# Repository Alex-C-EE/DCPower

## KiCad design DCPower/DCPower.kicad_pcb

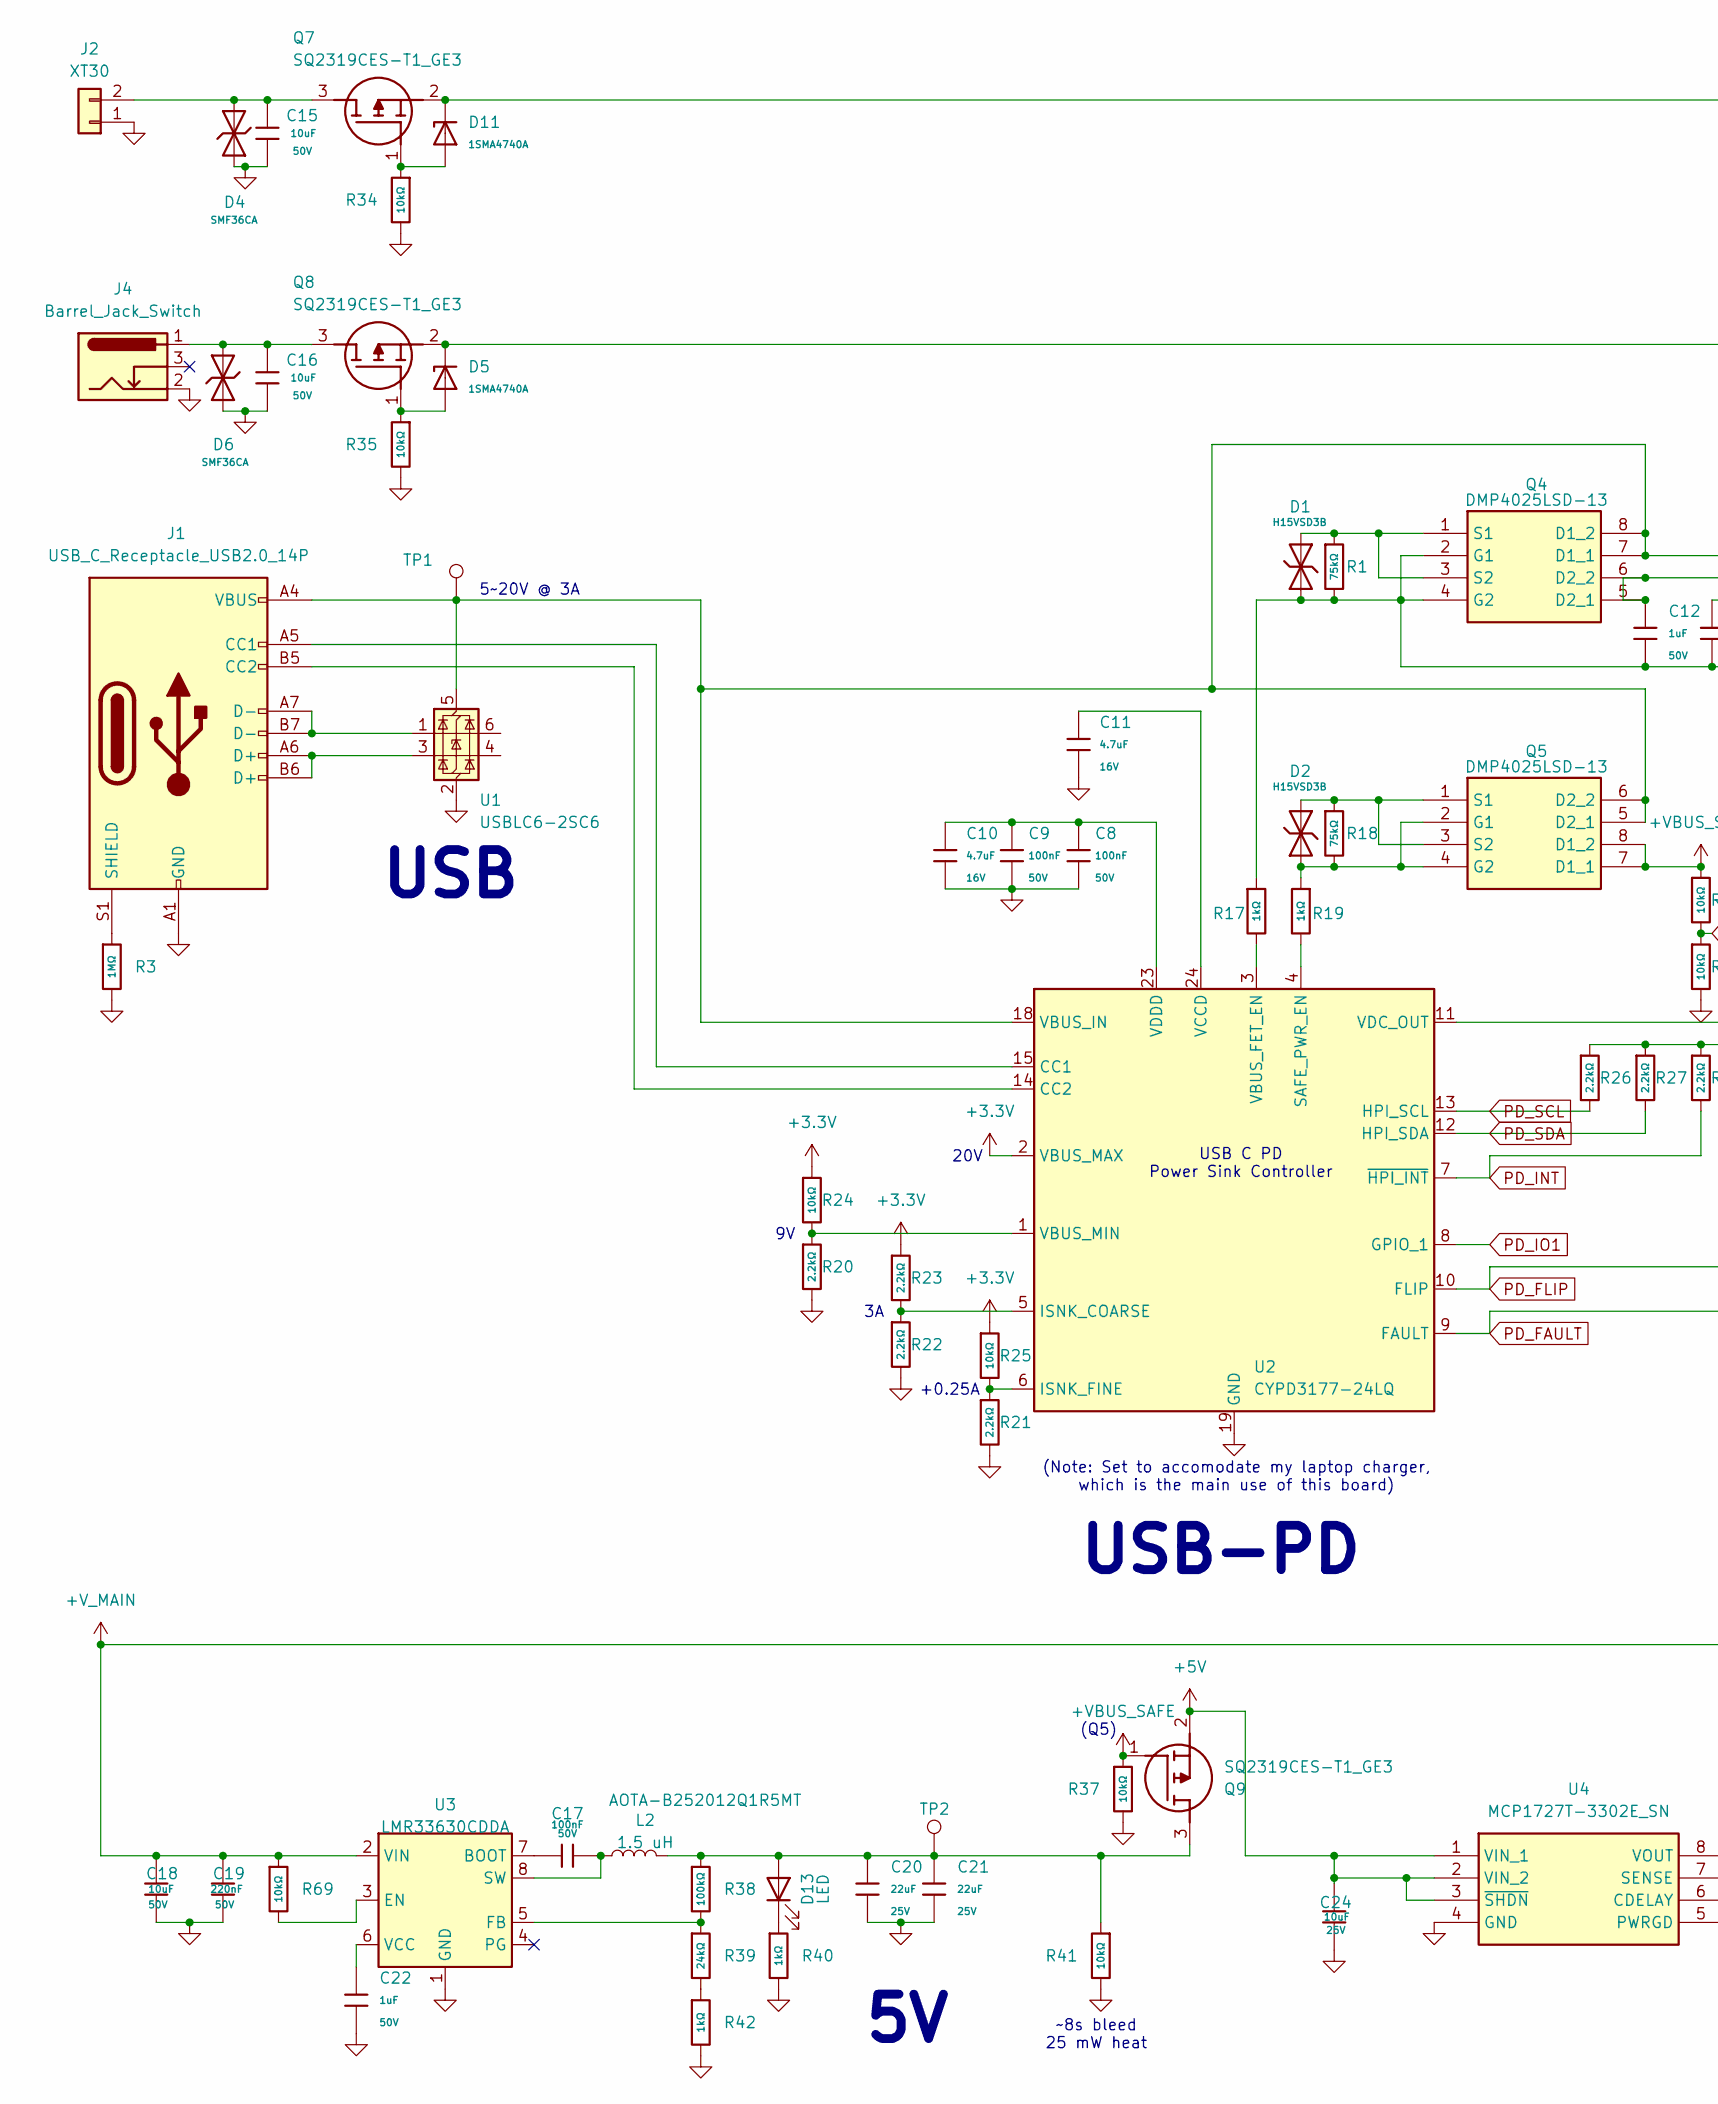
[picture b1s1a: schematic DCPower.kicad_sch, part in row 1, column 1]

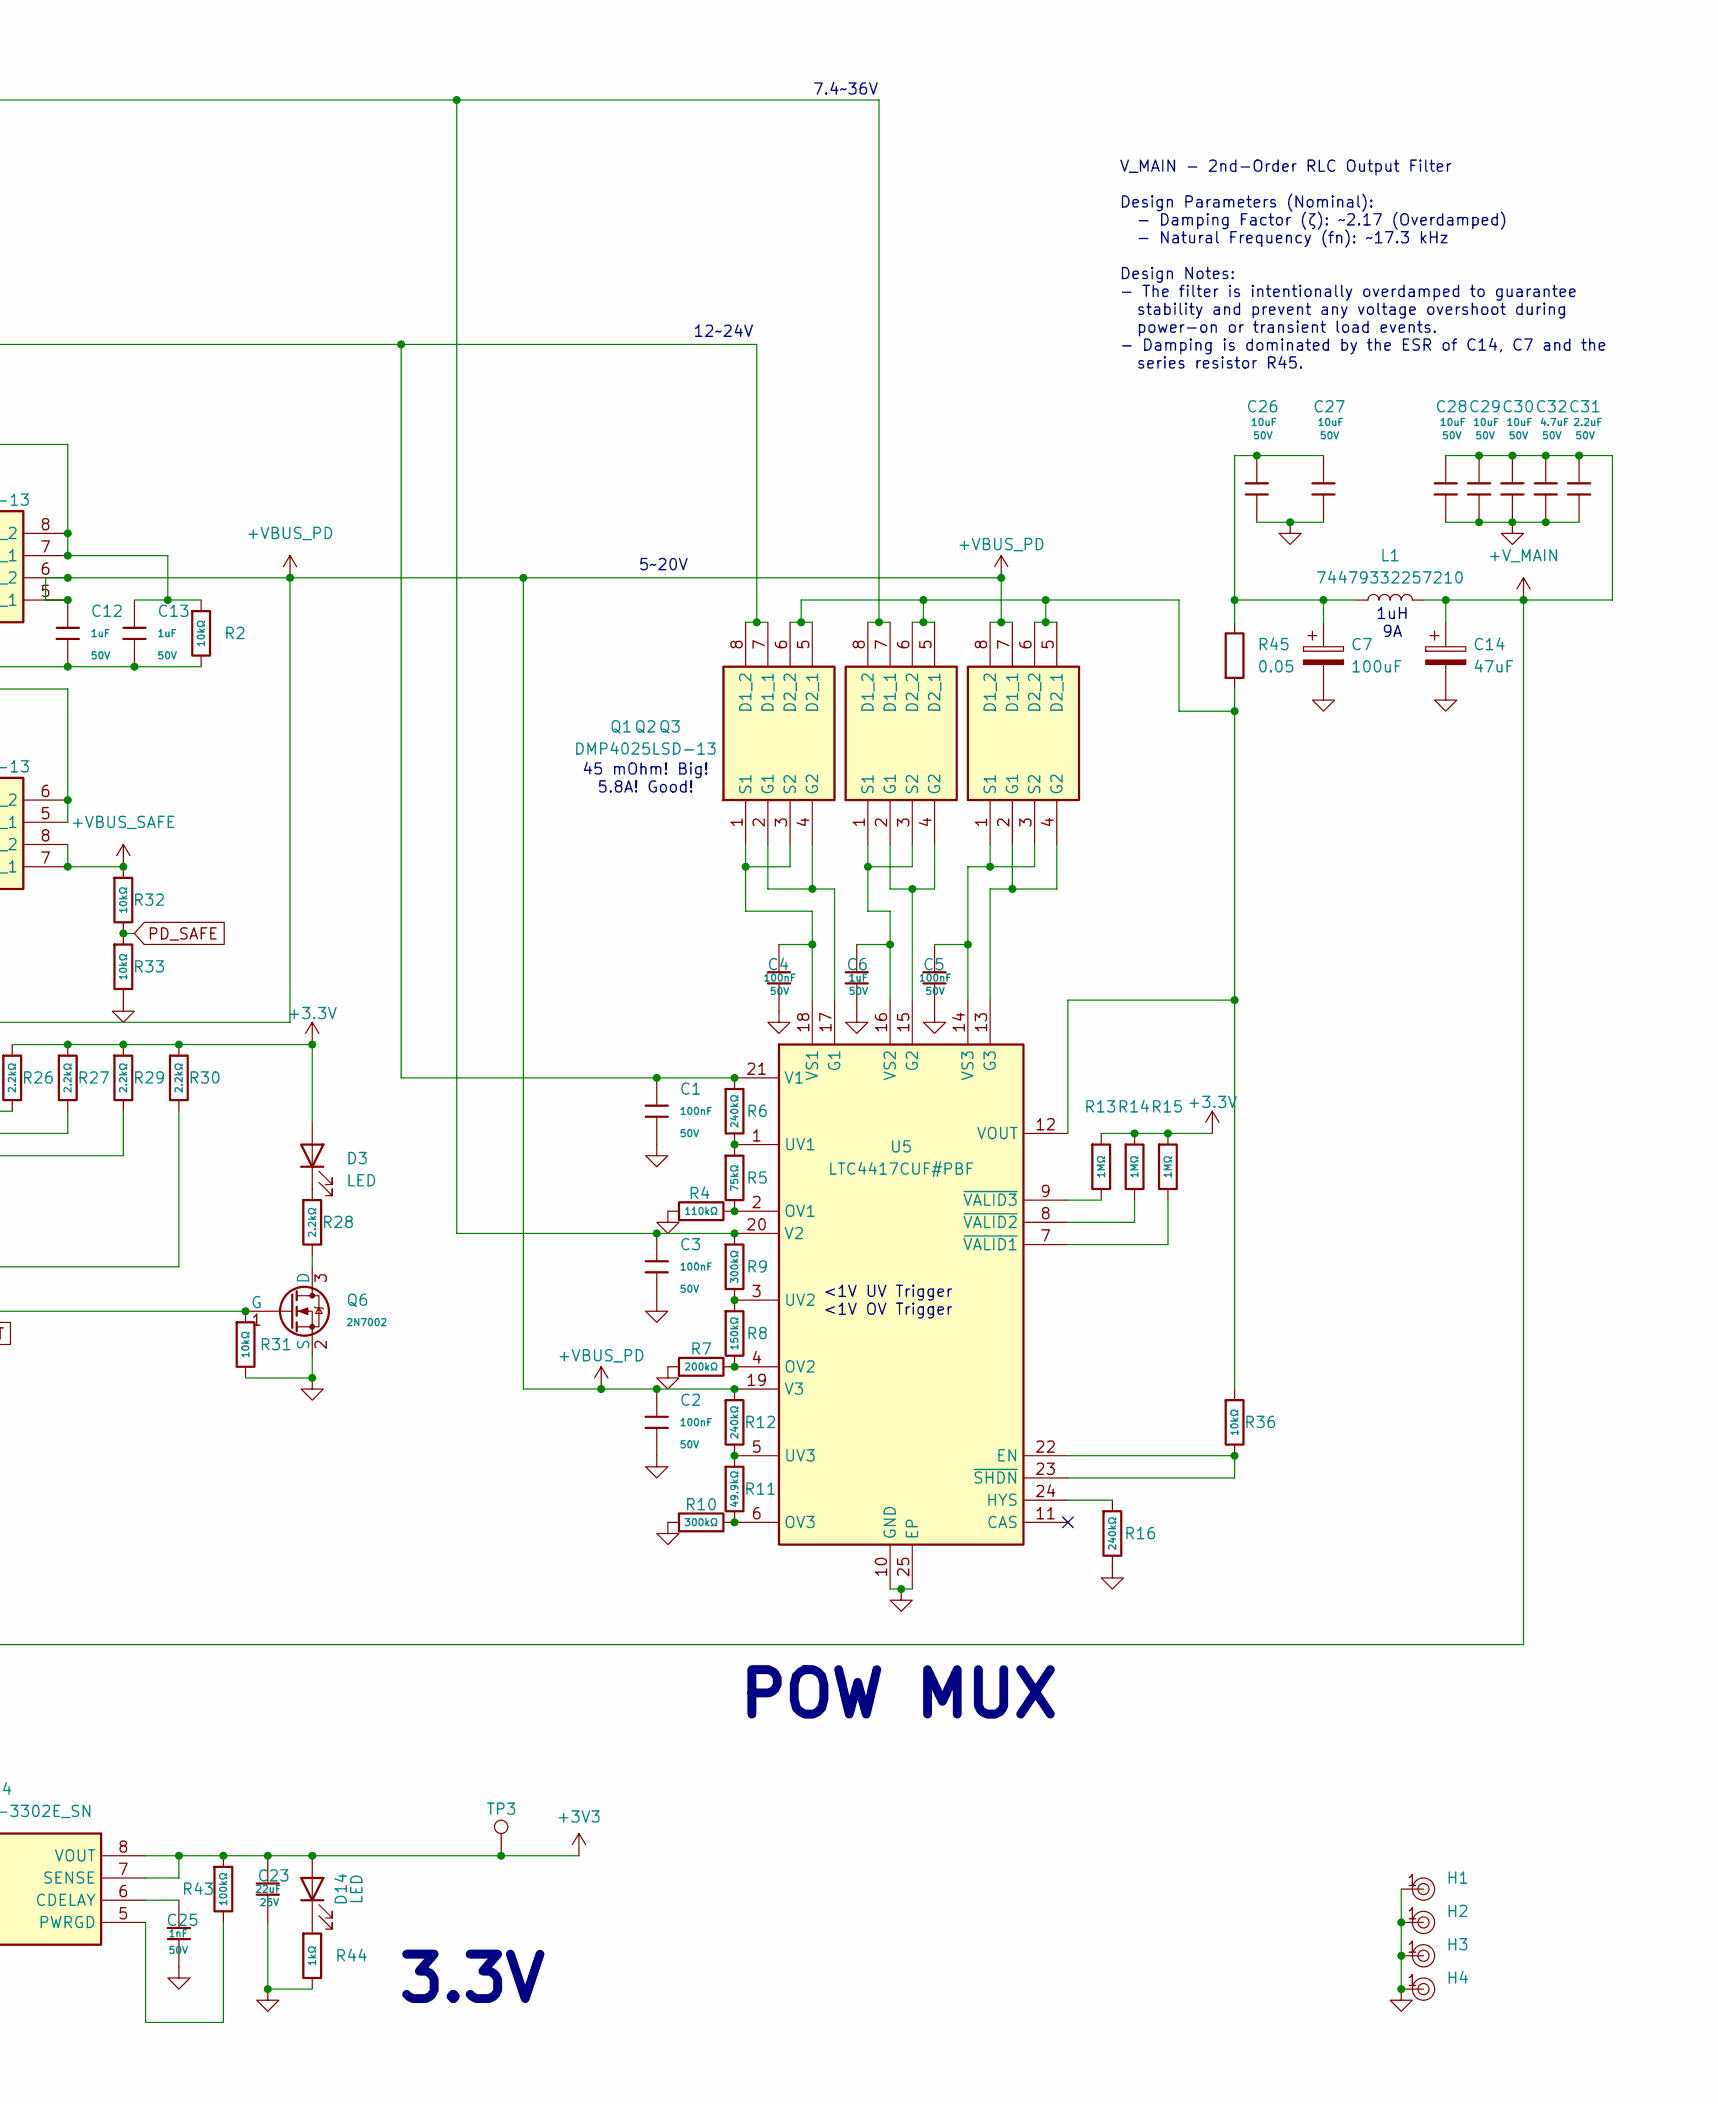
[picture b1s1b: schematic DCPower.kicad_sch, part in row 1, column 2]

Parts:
C1, C2, C3, C4, C5, C8, C9, C17: 100nF; C_0603; Voltage Rated 50V; Tolerance ±10%; Part CC0603KRX7R9BB104; LCSC C14663
C6, C12, C13: 1uF; C_0603; Voltage Rated 50V; Tolerance ±10%; Part CL10A105KB8NNNC; LCSC C15849
C7: 100uF; CAPAE830X1100N
C10, C11: 4.7uF; C_0603; Voltage Rated 16V; Tolerance ±10%; Part CL10A475KO8NNNC; LCSC C19666
C14: 47uF; EEEHP1H4R7P
C15, C16, C18: 10uF; C_0805; Voltage Rated 50V; Tolerance ±10%; Part GRM21BR61H106KE43L; LCSC C440198
C19: 220nF; C_0805; Voltage Rated 50V; Tolerance ±10%; Part CL21B224KBFNNNE; LCSC C5378
C20, C21, C23: 22uF; C_0805; Voltage Rated 25V; Tolerance ±20%; Part CL21A226MAQNNNE; LCSC C45783
C22: 1uF; C_0805; Voltage Rated 50V; Tolerance ±10%; Part CL21B105KBFNNNE; LCSC C28323
C24: 10uF; C_0805; Voltage Rated 25V; Tolerance ±10%; Part CL21A106KAYNNNE; LCSC C15850
C25: 1nF; C_0603; Voltage Rated 50V; Tolerance ±10%; Part CL10B102KB8NNNC; LCSC C1588
C26, C27, C28, C29, C30: 10uF; C_1206; Voltage Rated 50V; Tolerance ±10%; Part CL31A106KBHNNNE; LCSC C13585
C31: 2.2uF; C_0805; Voltage Rated 50V; Tolerance ±10%; Part CL21A225KBQNNNE; LCSC C377773
C32: 4.7uF; C_1206; Voltage Rated 50V; Tolerance ±10%; Part 1206B475K500NT; LCSC C29823
D1, D2: H15VSD3B; D_SOD-323; Part H15VSD3B; LCSC C20615814
D3, D13, D14: LED; LED_0603_1608Metric
D4, D6: SMF36CA; D_SOD-123FL; Part SMF36CA; LCSC C19077521
D5, D11: 1SMA4740A; D_SMA; Part 1SMA4740A; LCSC C19077479
H1, H2, H3, H4: Hole, 3mm
J1: USB_C_Receptacle_USB2.0_14P; USB_C_Receptacle_GCT_USB4105-xx-A_16P_TopMnt_Horizontal
J2: XT30; AMASS_XT30PW-M_1x02_P2.50mm_Horizontal
J4: Barrel_Jack_Switch; 694106301002_1
L1: 74479332257210; L_TDK_NLV32_3.2x2.5mm
L2: 1.5 uH; L_1008_2520Metric
Q1, Q2, Q3, Q4, Q5: DMP4025LSD-13; SOIC127P600X175-8N; Mouser Part Number 621-DMP4025LSD-13
Q6: 2N7002; Q_SOT-23; Part 2N7002; LCSC C8545
Q7, Q8, Q9: SQ2319CES-T1_GE3; SOT95P237X112-3N; Mouser Part Number 78-SQ2319CES-T1_GE3
R1, R5, R18: 75kΩ; R_0603; Overload Voltage (Max) 75V; Tolerance ±1%; Part 0603WAF7502T5E; LCSC C23242
R2, R24, R25, R31, R32, R33, R36, R37, R41, R69: 10kΩ; R_0603; Overload Voltage (Max) 75V; Tolerance ±1%; Part 0603WAF1002T5E; LCSC C25804
R3, R13, R14, R15: 1MΩ; R_0603; Overload Voltage (Max) 75V; Tolerance ±1%; Part 0603WAF1004T5E; LCSC C22935
R4: 110kΩ; R_0603; Overload Voltage (Max) 75V; Tolerance ±1%; Part 0603WAF1103T5E; LCSC C25805
R6, R12, R16: 240kΩ; R_0603; Overload Voltage (Max) 75V; Tolerance ±1%; Part 0603WAF2403T5E; LCSC C4197
R7: 200kΩ; R_0603; Overload Voltage (Max) 75V; Tolerance ±1%; Part 0603WAF2003T5E; LCSC C25811
R8: 150kΩ; R_0603; Overload Voltage (Max) 75V; Tolerance ±1%; Part 0603WAF1503T5E; LCSC C22807
R9, R10: 300kΩ; R_0603; Overload Voltage (Max) 75V; Tolerance ±1%; Part 0603WAF3003T5E; LCSC C23024
R11: 49.9kΩ; R_0603; Overload Voltage (Max) 75V; Tolerance ±1%; Part 0603WAF4992T5E; LCSC C23184
R17, R19, R40, R42, R44: 1kΩ; R_0603; Overload Voltage (Max) 75V; Tolerance ±1%; Part 0603WAF1001T5E; LCSC C21190
R20, R21, R22, R23, R26, R27, R28, R29, R30: 2.2kΩ; R_0603; Overload Voltage (Max) 75V; Tolerance ±1%; Part 0603WAF2201T5E; LCSC C4190
R34, R35: 10kΩ; R_0805; Overload Voltage (Max) 150V; Tolerance ±1%; Part 0805W8F1002T5E; LCSC C17414
R38, R43: 100kΩ; R_0603; Overload Voltage (Max) 75V; Tolerance ±1%; Part 0603WAF1003T5E; LCSC C25803
R39: 24kΩ; R_0603; Overload Voltage (Max) 75V; Tolerance ±1%; Part 0603WAF2402T5E; LCSC C23352
R45: 0.05
TP1: TestPoint; TestPoint_Pad_D1.0mm
TP2, TP3: TestPoint; TestPoint_Pad_D1.5mm
U1: USBLC6-2SC6; SOT-23-6
U2: CYPD3177-24LQ; QFN-24-1EP_4x4mm_P0.5mm_EP2.75x2.75mm
U3: LMR33630CDDA; Texas_HSOP-8-1EP_3.9x4.9mm_P1.27mm_ThermalVias
U4: MCP1727T-3302E_SN; SOIC127P600X175-8N; Mouser Part Number 579-MCP1727T-3302ESN
U5: LTC4417CUF#PBF; QFN50P400X400X80-25N-D; Mouser Part Number 584-LTC4417CUF#PBF

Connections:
+3.3V: D3.2 (A), R13.1, R14.1, R15.1, R23.1, R24.1, R25.1, R26.1, R27.1, R29.1, R30.1, U2.2 (VBUS_MAX)
+3V3: C23.1, D14.2 (A), R43.1, TP3.1, U4.7 (SENSE), U4.8 (VOUT)
+5V: C24.1, Q9.2 (S), U4.1 (VIN_1), U4.2 (VIN_2), U4.3 (~SHDN)
+VBUS_PD: C2.1, C12.1, Q3.7 (D1_1), Q3.8 (D1_2), Q4.5 (D2_1), Q4.6 (D2_2), R12.1, U2.11 (VDC_OUT), U5.19 (V3)
+VBUS_SAFE: Q5.7 (D1_1), Q5.8 (D1_2), Q9.1 (G), R32.1, R37.1
+V_MAIN: C14.1, C18.1, C19.1, C28.1, C29.1, C30.1, C31.1, C32.1, L1.2, R69.1, U3.2 (VIN)
GND: C1.2, C2.2, C3.2, C4.2, C5.2, C6.2, C7.2, C8.2, C9.2, C10.2, C11.2, C14.2, C15.2, C16.2, C18.2, C19.2, C20.2, C21.2, C22.2, C23.2, C24.2, C25.1, C26.2, C27.2, C28.2, C29.2, C30.2, C31.2, C32.2, D4.1, D6.1, H1.1, H2.1, H3.1, H4.1, J1.A1 (GND), J1.A12 (GND), J1.B1 (GND), J1.B12 (GND), J2.1, J4.2, Q6.2 (S), R3.2, R4.1, R7.1, R10.1, R16.2, R20.2, R21.2, R22.2, R31.2, R33.2, R34.2, R35.2, R37.2, R40.2, R41.2, R42.2, R44.2, U1.2 (GND), U2.19 (GND), U3.1 (GND), U3.9 (GND), U4.4 (GND), U5.10 (GND), U5.25 (EP)
unnamed: C7.1, C26.1, C27.1, L1.1, R45.1
unnamed: D3.1 (K), R28.1
unnamed: C20.1, C21.1, D13.2 (A), L2.2, Q9.3 (D), R38.1, R41.1, TP2.1
unnamed: D13.1 (K), R40.1
unnamed: D14.1 (K), R44.1
unnamed: J1.A5 (CC1), U2.15 (CC1)
unnamed: J1.B5 (CC2), U2.14 (CC2)
unnamed: J1.A6 (D+), J1.B6 (D+), U1.3 (I/O2)
unnamed: J1.A7 (D-), J1.B7 (D-), U1.1 (I/O1)
unnamed: J1.S1 (SHIELD), R3.1
unnamed: C15.1, D4.2, J2.2, Q7.3 (D)
unnamed: C1.1, D5.1, Q1.7 (D1_1), Q1.8 (D1_2), Q8.2 (S), R6.1, U5.21 (V1)
unnamed: Q1.5 (D2_1), Q1.6 (D2_2), Q2.5 (D2_1), Q2.6 (D2_2), Q3.5 (D2_1), Q3.6 (D2_2), R36.1, R45.2, U5.12 (VOUT)
unnamed: Q1.2 (G1), Q1.4 (G2), U5.17 (G1)
unnamed: C4.1, Q1.1 (S1), Q1.3 (S2), U5.18 (VS1)
unnamed: C3.1, D11.1, Q2.7 (D1_1), Q2.8 (D1_2), Q7.2 (S), R9.1, U5.20 (V2)
unnamed: Q2.2 (G1), Q2.4 (G2), U5.15 (G2)
unnamed: C6.1, Q2.1 (S1), Q2.3 (S2), U5.16 (VS2)
unnamed: Q3.2 (G1), Q3.4 (G2), U5.13 (G3)
unnamed: C5.1, Q3.1 (S1), Q3.3 (S2), U5.14 (VS3)
unnamed: C13.1, J1.A4 (VBUS), J1.A9 (VBUS), J1.B4 (VBUS), J1.B9 (VBUS), Q4.7 (D1_1), Q4.8 (D1_2), Q5.5 (D2_1), Q5.6 (D2_2), R2.1, TP1.1, U1.5 (VBUS), U2.18 (VBUS_IN)
unnamed: C12.2, C13.2, D1.1, Q4.2 (G1), Q4.4 (G2), R1.2, R2.2, R17.1
unnamed: D1.2, Q4.1 (S1), Q4.3 (S2), R1.1
unnamed: D2.1, Q5.2 (G1), Q5.4 (G2), R18.2, R19.1
unnamed: D2.2, Q5.1 (S1), Q5.3 (S2), R18.1
unnamed: Q6.3 (D), R28.2
unnamed: D11.2, Q7.1 (G), R34.1
unnamed: C16.1, D6.2, J4.1, Q8.3 (D)
unnamed: D5.2, Q8.1 (G), R35.1
unnamed: R39.2, R42.1
unnamed: U2.22 (GND), U2.25 (GND)
unnamed: R22.1, R23.2, U2.5 (ISNK_COARSE)
unnamed: R21.1, R25.2, U2.6 (ISNK_FINE)
unnamed: R19.2, U2.4 (SAFE_PWR_EN)
unnamed: R17.2, U2.3 (VBUS_FET_EN)
unnamed: R20.1, R24.2, U2.1 (VBUS_MIN)
unnamed: C11.1, U2.24 (VCCD)
unnamed: C8.1, C9.1, C10.1, U2.23 (VDDD)
unnamed: C17.1, U3.7 (BOOT)
unnamed: R69.2, U3.3 (EN)
unnamed: R38.2, R39.1, U3.5 (FB)
unnamed: C17.2, L2.1, U3.8 (SW)
unnamed: C22.1, U3.6 (VCC)
unnamed: C25.2, U4.6 (CDELAY)
unnamed: R43.2, U4.5 (PWRGD)
unnamed: R36.2, U5.22 (EN), U5.23 (~SHDN)
unnamed: R16.1, U5.24 (HYS)
unnamed: R4.2, R5.2, U5.2 (OV1)
unnamed: R7.2, R8.2, U5.4 (OV2)
unnamed: R10.2, R11.2, U5.6 (OV3)
unnamed: R5.1, R6.2, U5.1 (UV1)
unnamed: R8.1, R9.2, U5.3 (UV2)
unnamed: R11.1, R12.2, U5.5 (UV3)
unnamed: R15.2, U5.7 (~VALID1)
unnamed: R14.2, U5.8 (~VALID2)
unnamed: R13.2, U5.9 (~VALID3)
PD_FAULT: Q6.1 (G), R31.1, U2.9 (FAULT)
PD_FLIP: R30.2, U2.10 (FLIP)
PD_INT: R29.2, U2.7 (~HPI_INT)
PD_IO1: U2.8 (GPIO_1)
PD_SAFE: R32.2, R33.1
PD_SCL: R26.2, U2.13 (HPI_SCL)
PD_SDA: R27.2, U2.12 (HPI_SDA)

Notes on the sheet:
5~20V @ 3A
12~24V
USB-PD
~8s bleed 25 mW heat
+0.25A
POW MUX
45 mOhm! Big! 5.8A! Good!
(Q5)
3.3V
7.4~36V
5~20V
V_MAIN - 2nd-Order RLC Output Filter Design Parameters (Nominal): - Damping Factor (ζ): ~2.17 (Overdamped) - Natural Frequency (fn): ~17.3 kHz Design Notes: - The filter is intentionally overdamped to guarantee stability and prevent any voltage overshoot during power-on or transient load events. - 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
20V
<1V UV Trigger <1V OV Trigger
1uH 9A
(Note: Set to accomodate my laptop charger, which is the main use of this board)
USB
USB C PD Power Sink Controller

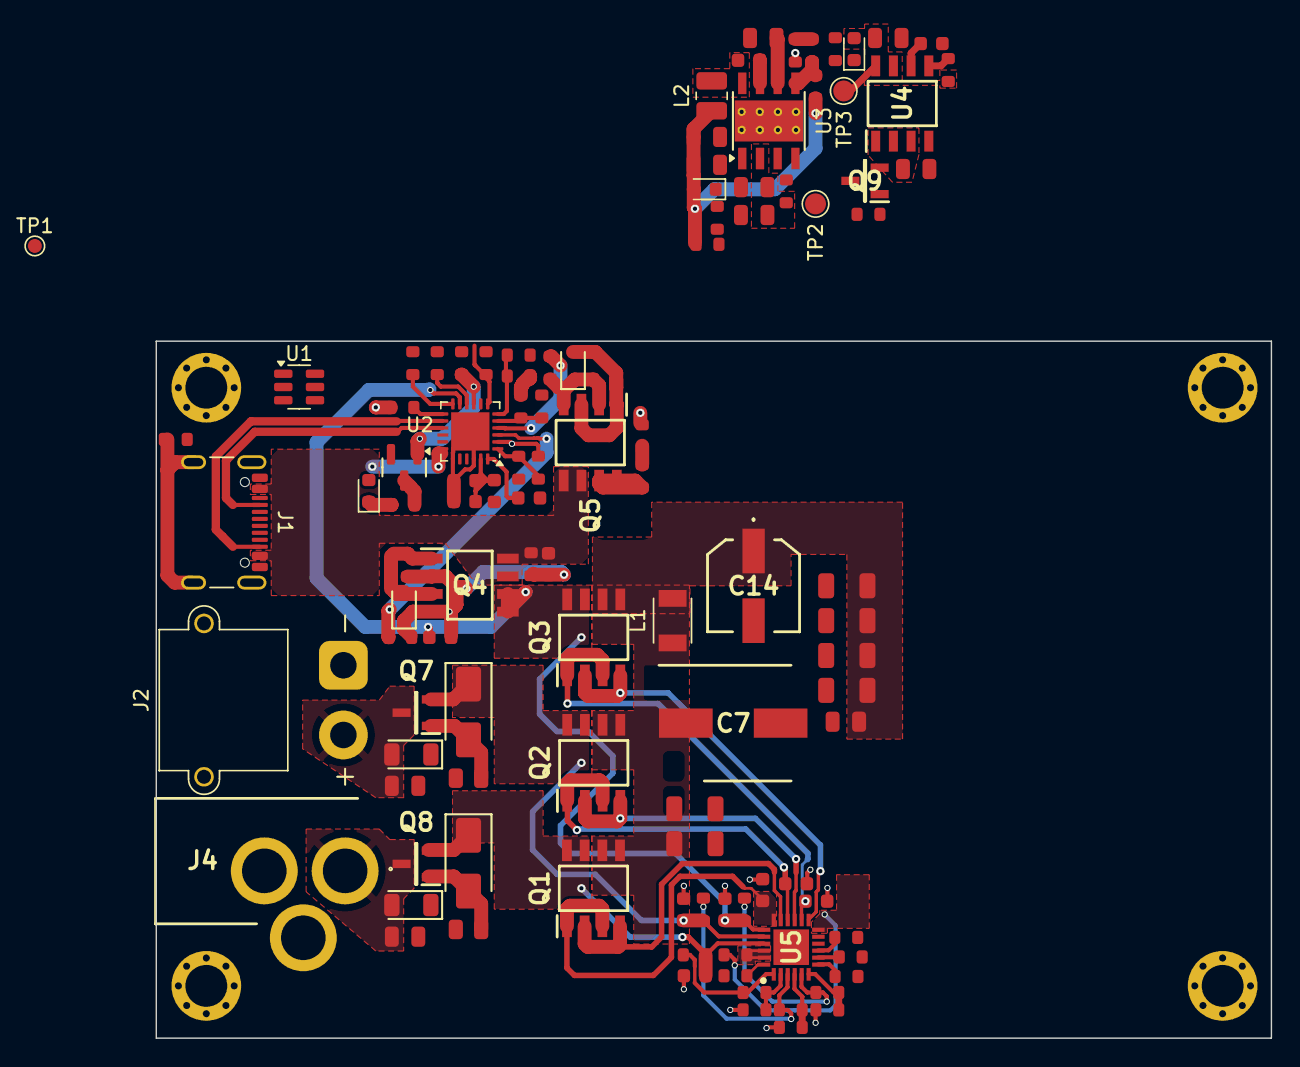
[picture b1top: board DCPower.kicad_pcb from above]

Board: 6 copper layers, 80.0 x 50.0 mm, 112 parts (0 on the bottom side), 69 nets.

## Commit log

2025-10-08 Input Stage
2025-10-09 More Power Path, fixed filter
2025-10-10 2nd Order RLC Simulation
2025-10-12 Forked into Simple 1 input version
2025-11-23 Regularizare
